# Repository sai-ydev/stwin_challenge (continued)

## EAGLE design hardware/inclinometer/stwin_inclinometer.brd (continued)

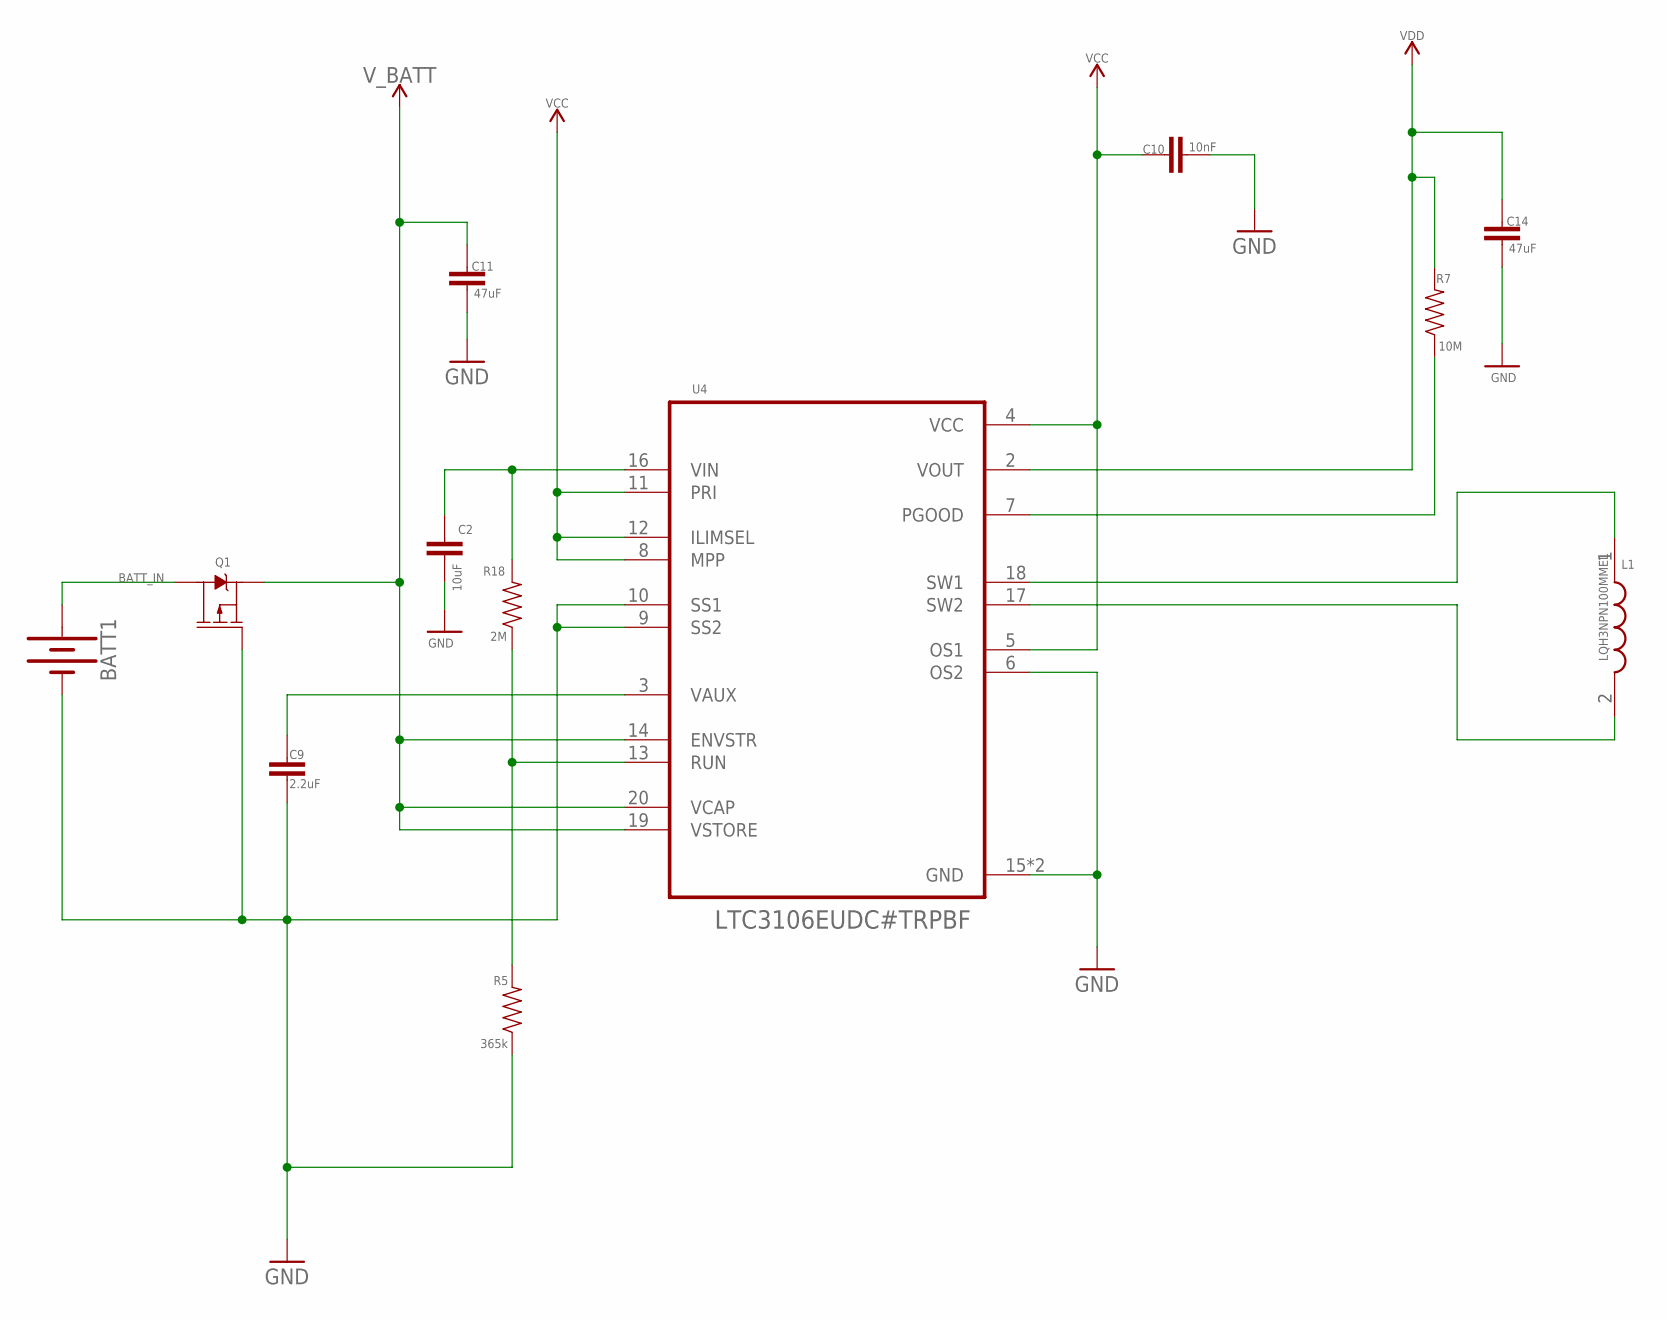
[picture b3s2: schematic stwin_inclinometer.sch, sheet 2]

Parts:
BATT1: KEYSTONE_54KEYSTONE_2; KEYSTONE_V2
C2: 10uF; 0603
C9: 2.2uF; 0603
C10: 10nF; 0603
C11, C14: 47uF; 0603
L1: LQH3NPN100MMEL; INDPM3030X150N
Q1: 2.5A/30V/105mΩ; SOT23-3
R5: 365k; 0603
R7: 10M; 0603
R18: 2M; 0603
U4: LTC3106EUDC#TRPBF; QFN50P400X300X80-21N

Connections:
BATT_IN: BATT1.P$1 (+), BATT1.P$2 (+), BATT1.P$3 (+), Q1.3 (D)
GND: BATT1.P$4 (-), BATT1.P$5 (-), BATT1.P$6 (-), C2.2, C9.2, C10.2, C11.2, C14.2, Q1.1 (G), R5.1, U4.6 (OS2), U4.9 (SS2), U4.10 (SS1), U4.15 (GND), U4.21 (GND); also elsewhere on the board
unnamed: L1.1, U4.18 (SW1)
unnamed: L1.2, U4.17 (SW2)
unnamed: R7.1, U4.7 (PGOOD)
unnamed: C9.1, U4.3 (VAUX)
unnamed: C2.1, R18.2, U4.16 (VIN)
unnamed: R5.2, R18.1, U4.13 (RUN)
VCC: C10.1, U4.4 (VCC), U4.5 (OS1), U4.8 (MPP), U4.11 (PRI), U4.12 (ILIMSEL)
VDD: C14.1, R7.2, U4.2 (VOUT); also elsewhere on the board
V_BATT: C11.1, Q1.2 (S), U4.14 (ENVSTR), U4.19 (VSTORE), U4.20 (VCAP)

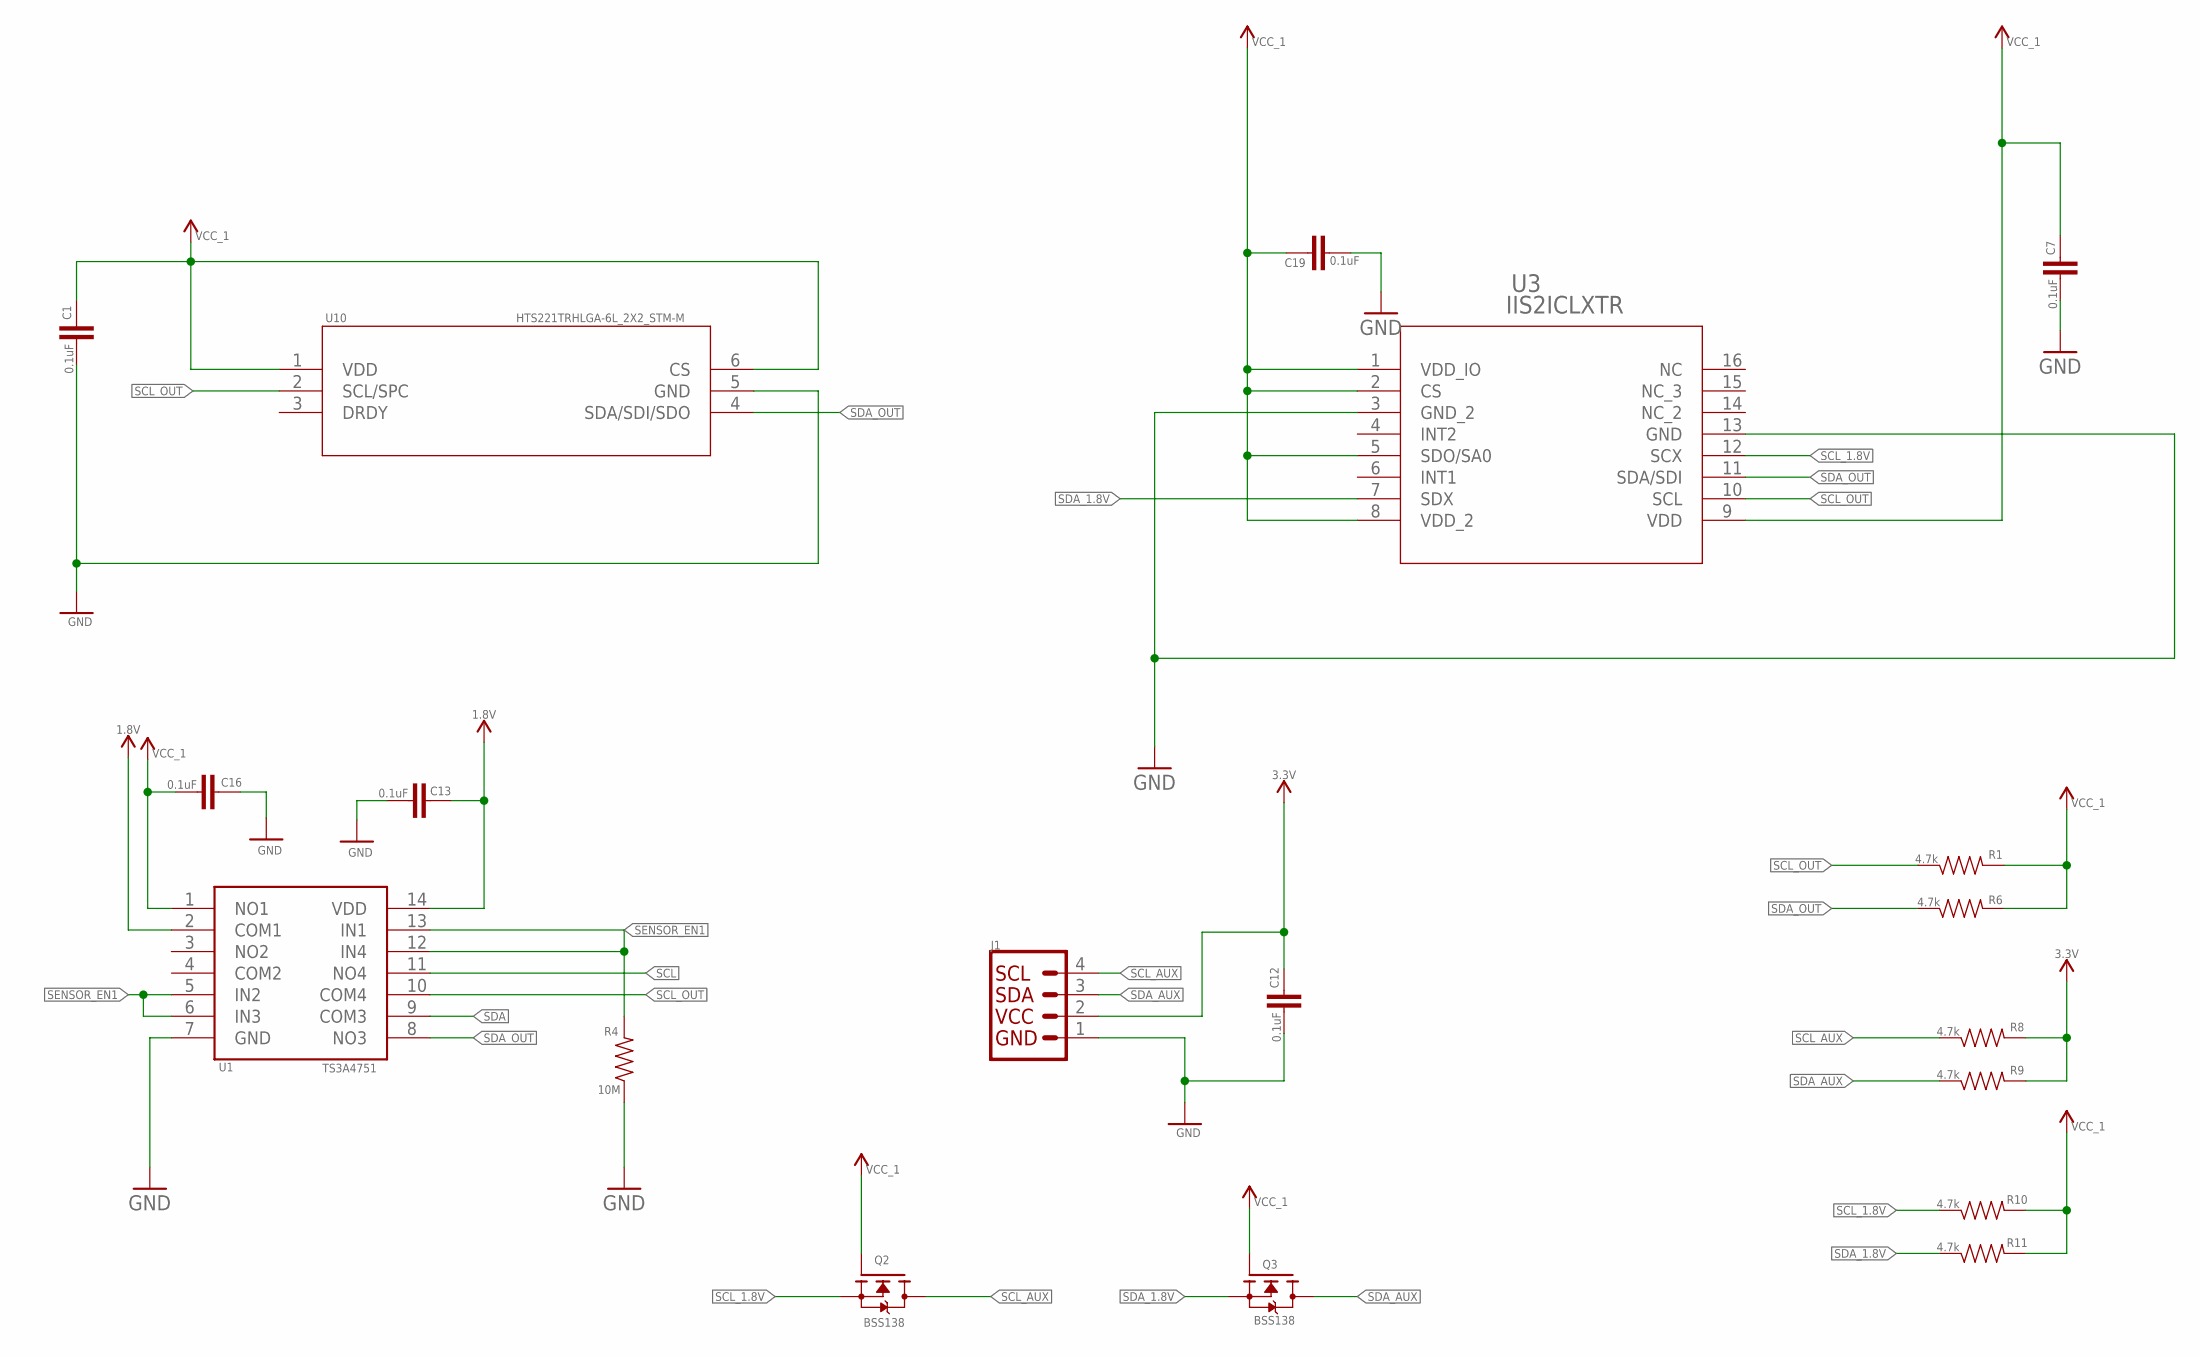
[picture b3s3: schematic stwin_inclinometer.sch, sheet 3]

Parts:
C1, C7, C12, C13, C16, C19: 0.1uF; 0603
J1: I2C_STANDARD; 1X04
Q2, Q3: BSS138; SOT95P240X111-3N
R1, R6, R8, R9, R10, R11: 4.7k; 0603
R4: 10M; 0603
U1: TS3A4751; 14_PIN
U3: IIS2ICLXTR; QFN_ICLX_STM
U10: HTS221TRHLGA-6L_2X2_STM-M; HLGA-6L_2X2_STM-M

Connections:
1.8V: C13.1, U1.2 (COM1), U1.14 (VDD); also elsewhere on the board
3.3V: C12.1, J1.2, R8.2, R9.2; also elsewhere on the board
GND: C1.2, C7.2, C12.2, C13.2, C16.1, C19.2, J1.1, R4.1, U1.7 (GND), U3.3 (GND_2), U3.13 (GND), U10.5 (GND); also elsewhere on the board
SCL: U1.11 (NO4); also elsewhere on the board
SCL_1.8V: Q2.2 (S), R10.1, U3.12 (SCX)
SCL_AUX: J1.4, Q2.3 (D), R8.1
SCL_OUT: R1.1, U1.10 (COM4), U3.10 (SCL), U10.2 (SCL/SPC)
SDA: U1.9 (COM3); also elsewhere on the board
SDA_1.8V: Q3.2 (S), R11.1, U3.7 (SDX)
SDA_AUX: J1.3, Q3.3 (D), R9.1
SDA_OUT: R6.1, U1.8 (NO3), U3.11 (SDA/SDI), U10.4 (SDA/SDI/SDO)
SENSOR_EN1: R4.2, U1.5 (IN2), U1.6 (IN3), U1.12 (IN4), U1.13 (IN1); also elsewhere on the board
VCC_1: C1.1, C7.1, C16.2, C19.1, Q2.1 (G), Q3.1 (G), R1.2, R6.2, R10.2, R11.2, U1.1 (NO1), U3.1 (VDD_IO), U3.2 (CS), U3.5 (SDO/SA0), U3.8 (VDD_2), U3.9 (VDD), U10.1 (VDD), U10.6 (CS)

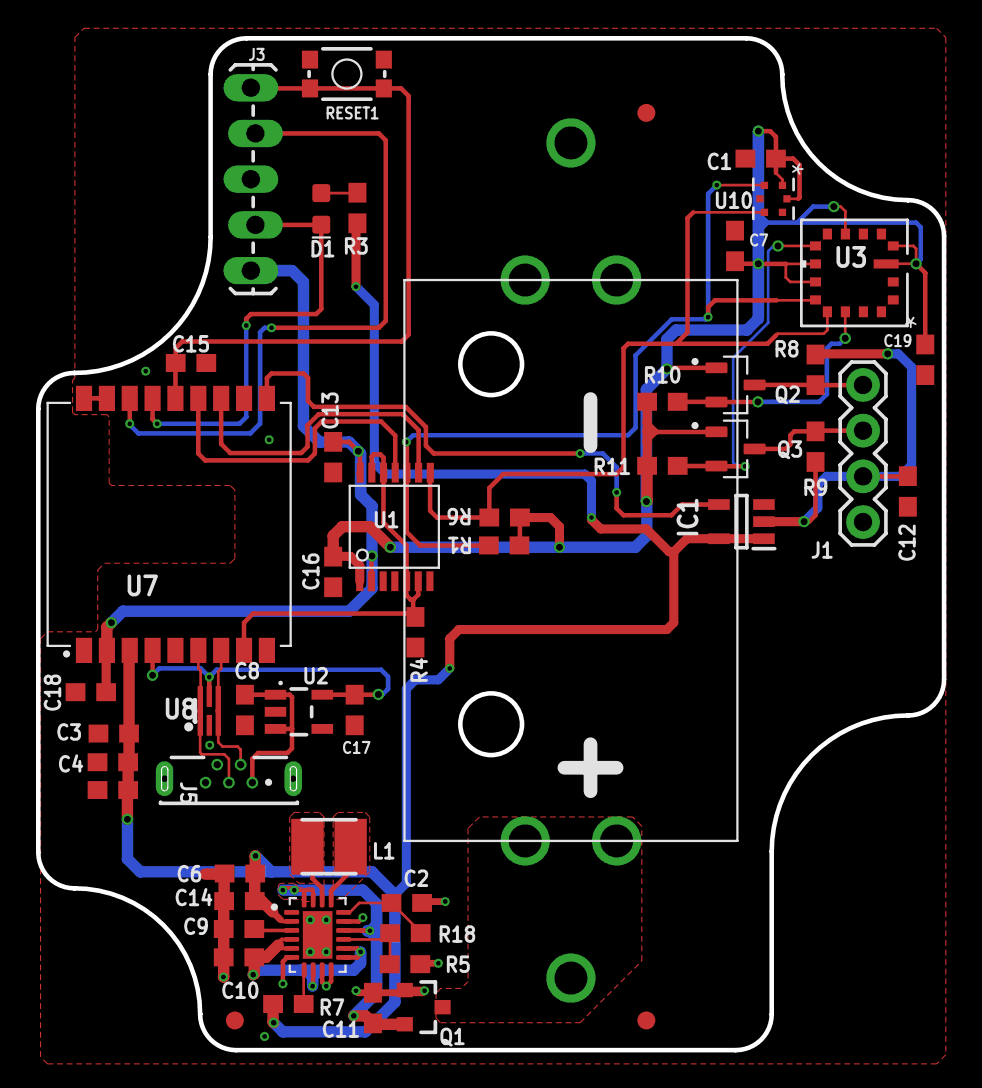
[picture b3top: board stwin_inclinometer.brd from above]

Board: 2 copper layers, 50.3 x 56.2 mm, 51 parts (0 on the bottom side), 34 nets.

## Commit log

2020-12-07 Design files check-in
2020-12-08 Uploading gerber files
2020-12-08 Check-in
2020-12-12 uploading images
2020-12-22 Check-in of BoM files
